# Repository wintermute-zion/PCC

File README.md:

# PCC (Physical Control Center)

PCC is a macropad with six keys and a rotary encoder. I designed it to control things like my PC's volume and media playback (hence the "Physical Control Center" name) but you can build a new firmware to map the keys to do anything, really.

Designed for Hack Club's Hackpad program. (view it [here](https://hackpad.hackclub.com))

## Disclaimer!

I haven't recieved my PCB or kit from Hack Club as of yet, so both the case and firmware code are not guaranteed to work with this macropad on the first try (the case may not fit, the firmware may reference a key that doesn't exist, I don't know). Obviously once I recieve everthing I will fix any problems that should arise, but until then, continue cautiously.

## Case

The case is in two parts, held together with screws driven through holes in the top case's corners. All screws in the case screw into heat-set inserts, so to allow easier disassembly, if that's something you'll need.

## Firmware

KMK firmware is used for this macropad, though I'm sure you could make a QMK version if you so please. I chose KMK since it uses Python though. View the firmware code [here.](https://github.com/wintermute-zion/PCC/blob/main/production/main.py)

## Pinouts

### Key Matrix

| Row/Column | Digital GPIO Pin | GPIO Pin |
| ---------- | ---------------- | -------- |
| Row 1      | D10              | GPIO3    |
| Row 2      | D9               | GPIO4    |
| Column 1   | D6               | GPIO0    |
| Column 2   | D7               | GPIO1    |
| Column 3   | D8               | GPIO2    |

### Rotary Encoder

| Pin | Digital GPIO Pin | GPIO Pin |
| --- | ---------------- | -------- |
| A   | D1               | GPIO27   |
| B   | D0               | GPIO26   |
| S1  | D2               | GPIO28   |

## Key Map

### Key Matrix

|       | Column 1             | Column 2         | Column 3           |
| ----- | -------------------- | ---------------- | ------------------ |
| Row 1 | Play/Pause Media     | Stop Track (Win) | Show Desktop (Win) |
| Row 2 | Previous Track (Win) | Next Track (Win) | Lock PC (Win)      |

### Rotrary Encoder

|                  |             |
| ---------------- | ----------- |
| Knob turn left   | Volume Down |
| Knob turn right  | Volume Up   |
| Knob button push | Audio Mute  |

## BOM

A list of everything you'd need to build this. You can view this as a .csv file [here.](https://github.com/wintermute-zion/PCC/blob/main/BOM%20.csv)

- (1) Seeed Studio XIAO RP2040 MCU
- (6) Cherry MX keyboard switches
- (1) EC11 rotary encoder
- (6) 1N4148 diodes
- (6) M3 x 5mm x 4mm heatset inserts
- (6) M3 x 16mm screws
- (6) Keycaps
- (1) Custom PCB
- (1) Case bottom
- (1) Case top

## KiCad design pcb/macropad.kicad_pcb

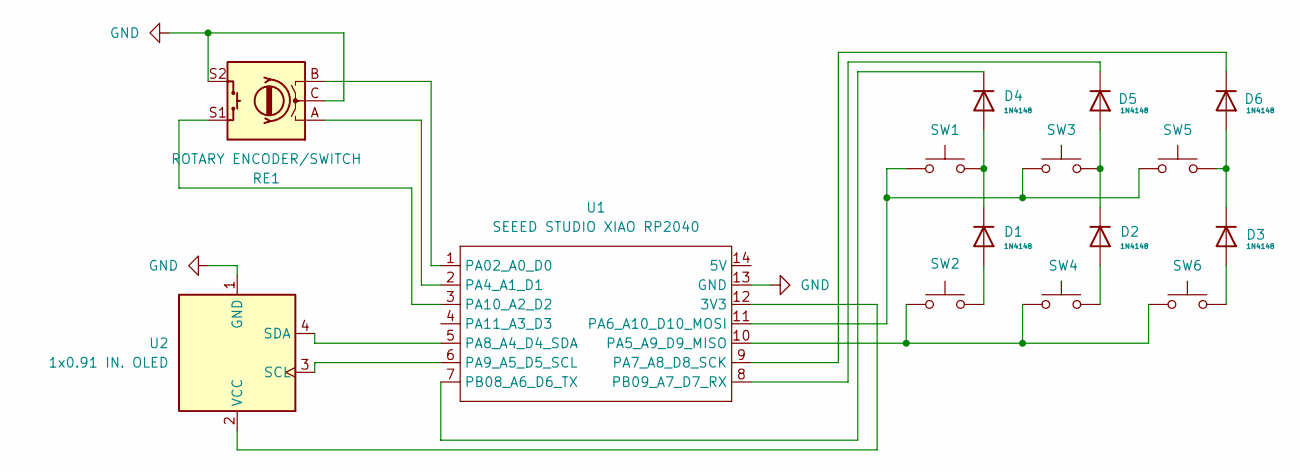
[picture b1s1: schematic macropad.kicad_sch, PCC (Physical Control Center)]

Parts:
D1, D2, D3, D4, D5, D6: 1N4148; D_DO-35_SOD27_P7.62mm_Horizontal
RE1: ROTARY ENCODER/SWITCH; RotaryEncoder_Alps_EC11E-Switch_Vertical_H20mm
SW1, SW2, SW3, SW4, SW5, SW6: SW_Push; SW_Cherry_MX_1.00u_PCB
U1: SEEED STUDIO XIAO RP2040; XIAO-Generic-Hybrid-14P-2.54-21X17.8MM
U2: 1x0.91 IN. OLED; ER_OLEDM0.91_1x-I2C

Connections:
GND: RE1.C, RE1.S2, U1.13 (GND), U2.1 (GND)
unnamed: D1.2 (A), SW2.2
unnamed: D1.1 (K), D4.2 (A), SW1.2
unnamed: D2.2 (A), SW4.2
unnamed: D2.1 (K), D5.2 (A), SW3.2
unnamed: D3.2 (A), SW6.2
unnamed: D3.1 (K), D6.2 (A), SW5.2
unnamed: D4.1 (K), U1.7 (PB08_A6_D6_TX)
unnamed: D5.1 (K), U1.8 (PB09_A7_D7_RX)
unnamed: D6.1 (K), U1.9 (PA7_A8_D8_SCK)
unnamed: U1.12 (3V3), U2.2 (VCC)
unnamed: RE1.B, U1.1 (PA02_A0_D0)
unnamed: RE1.A, U1.2 (PA4_A1_D1)
unnamed: SW2.1, SW4.1, SW6.1, U1.10 (PA5_A9_D9_MISO)
unnamed: SW1.1, SW3.1, SW5.1, U1.11 (PA6_A10_D10_MOSI)
unnamed: U1.5 (PA8_A4_D4_SDA), U2.4 (SDA)
unnamed: U1.6 (PA9_A5_D5_SCL), U2.3 (SCL)
unnamed: RE1.S1, U1.3 (PA10_A2_D2)

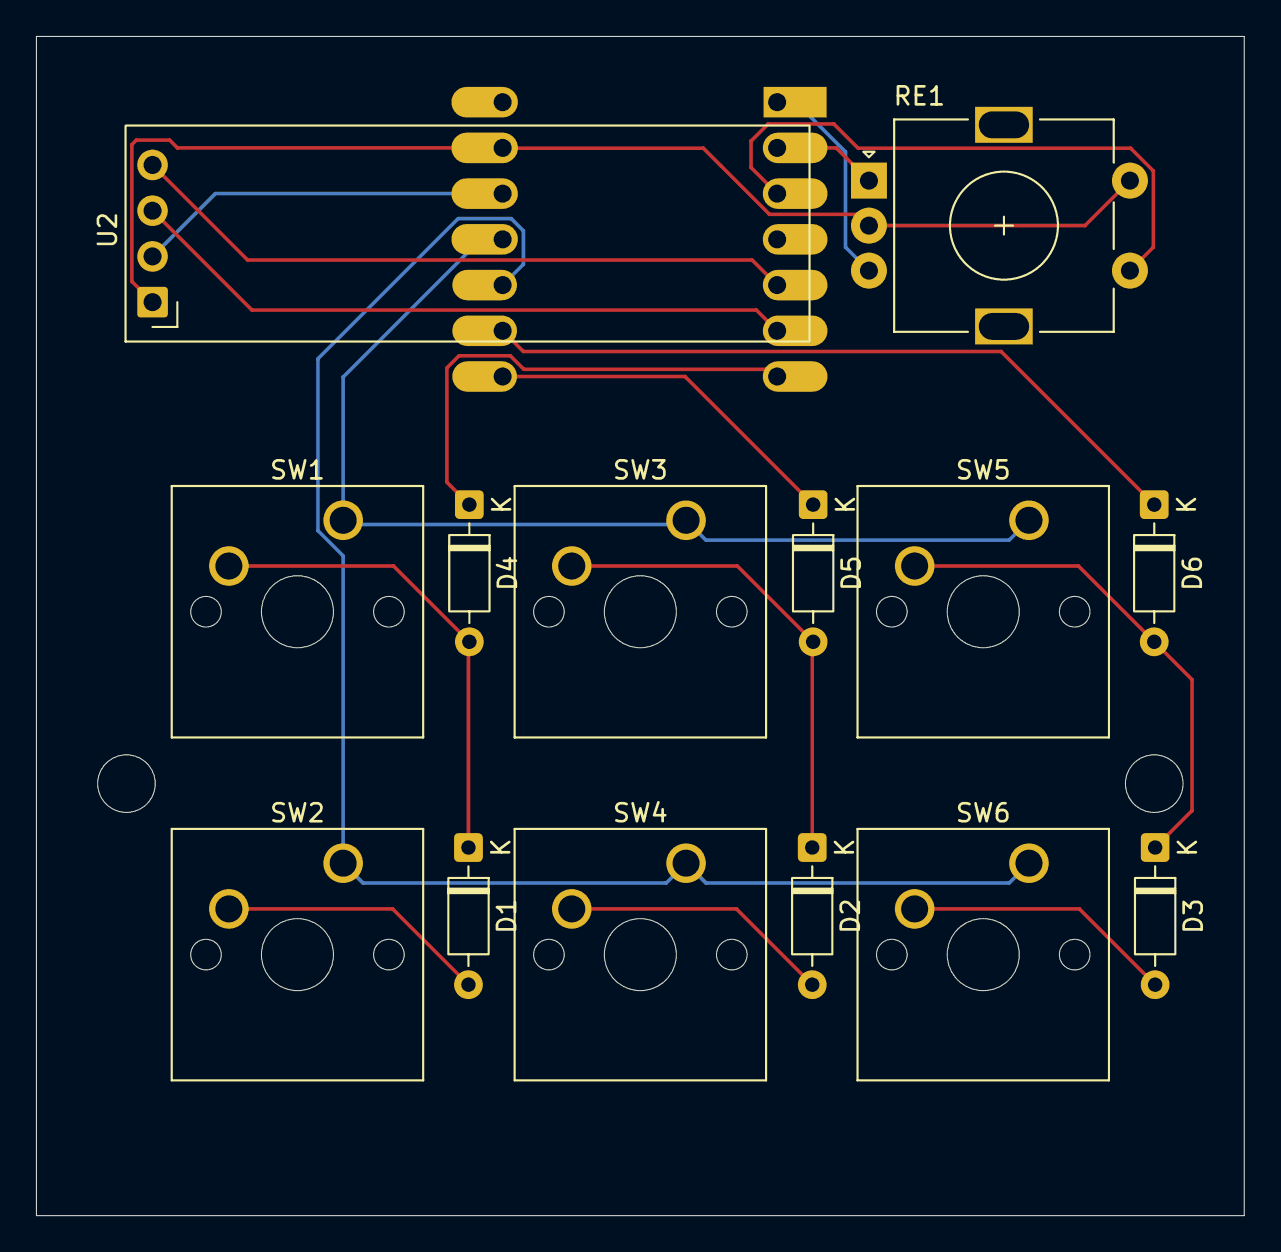
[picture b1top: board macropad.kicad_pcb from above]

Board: 2 copper layers, 67.1 x 65.5 mm, 15 parts (1 on the bottom side), 18 nets.
